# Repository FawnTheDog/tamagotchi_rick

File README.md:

# tamagotchi_rick
My twist on the starbie starter project for Hackclub's Halflife event.

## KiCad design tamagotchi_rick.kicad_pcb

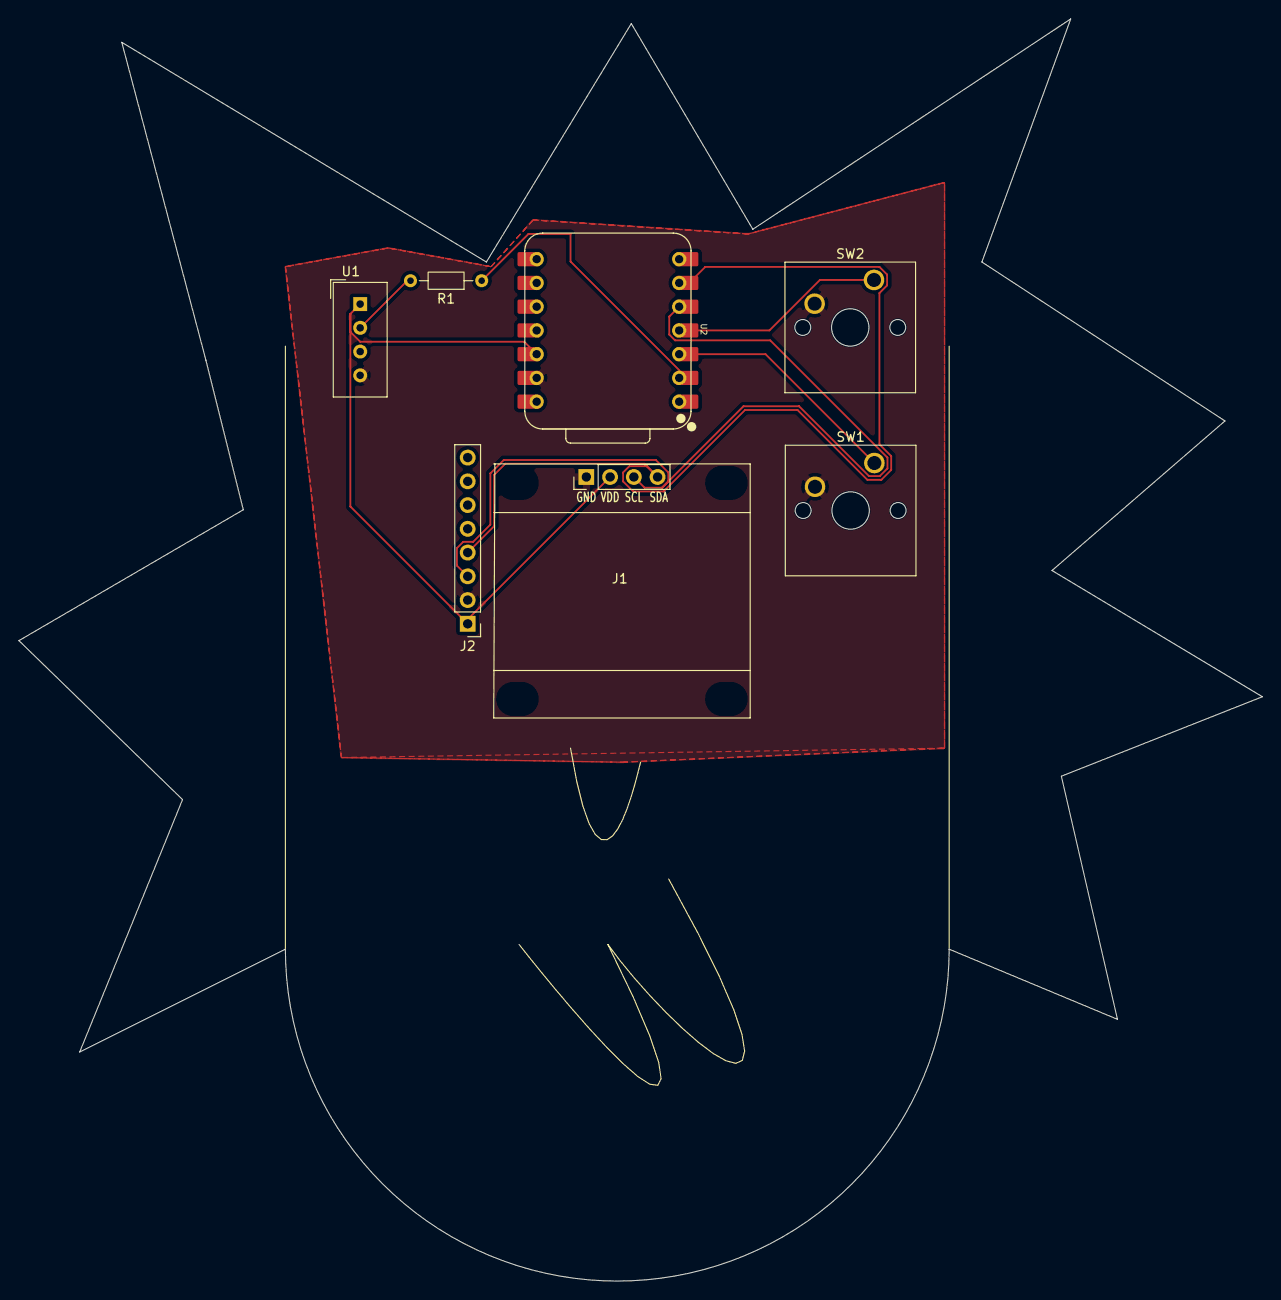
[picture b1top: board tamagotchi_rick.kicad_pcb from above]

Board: 2 copper layers, 133.0 x 135.0 mm, 7 parts (0 on the bottom side), 8 nets.

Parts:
J1: Conn_01x04_Pin; Display_128x64_096_I2C
J2: Conn_01x08_Pin; PinHeader_1x08_P2.54mm_Vertical
R1: 10k; R_Axial_DIN0204_L3.6mm_D1.6mm_P7.62mm_Horizontal
SW1, SW2: SW_Push; SW_Cherry_MX_1.00u_PCB
U1: DHT11; Aosong_DHT11_5.5x12.0_P2.54mm
U2: XIAO-ESP32-C3-SMD; XIAO-ESP32-C6-DIP

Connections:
+3.3V: J1.2, J2.1, U1.1 (VDD), U2.12 (3V3_OUT)
GND: J1.1, J2.2, SW1.2, SW2.2, U1.4 (GND), U2.13 (GND)
unnamed: J1.3, J2.3, U2.5 (D4)
unnamed: J1.4, J2.4, U2.6 (D5)
unnamed: R1.2, U1.2 (DATA)
unnamed: R1.1, U2.2 (D1)
unnamed: SW1.1, U2.3 (D2)
unnamed: SW2.1, U2.4 (D3)
